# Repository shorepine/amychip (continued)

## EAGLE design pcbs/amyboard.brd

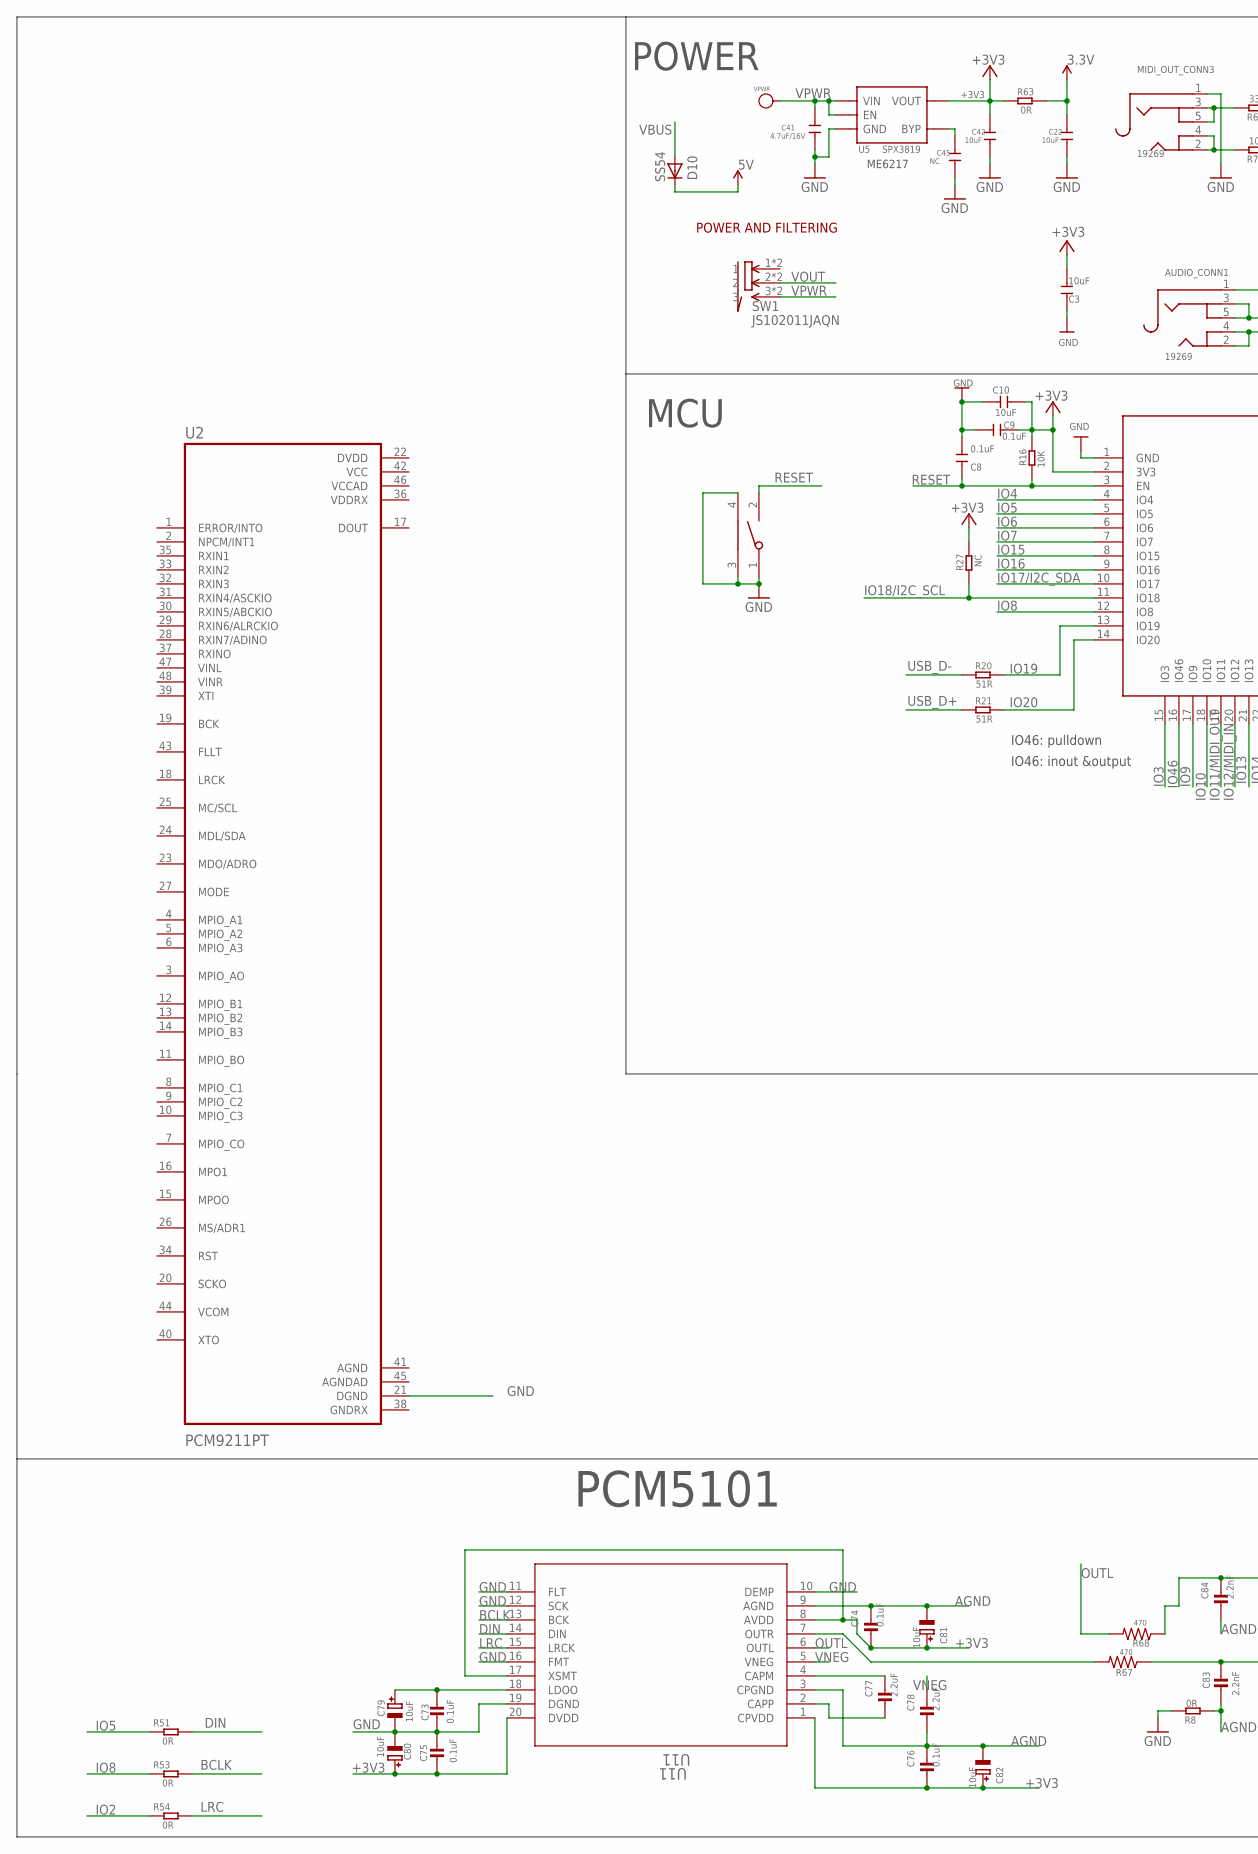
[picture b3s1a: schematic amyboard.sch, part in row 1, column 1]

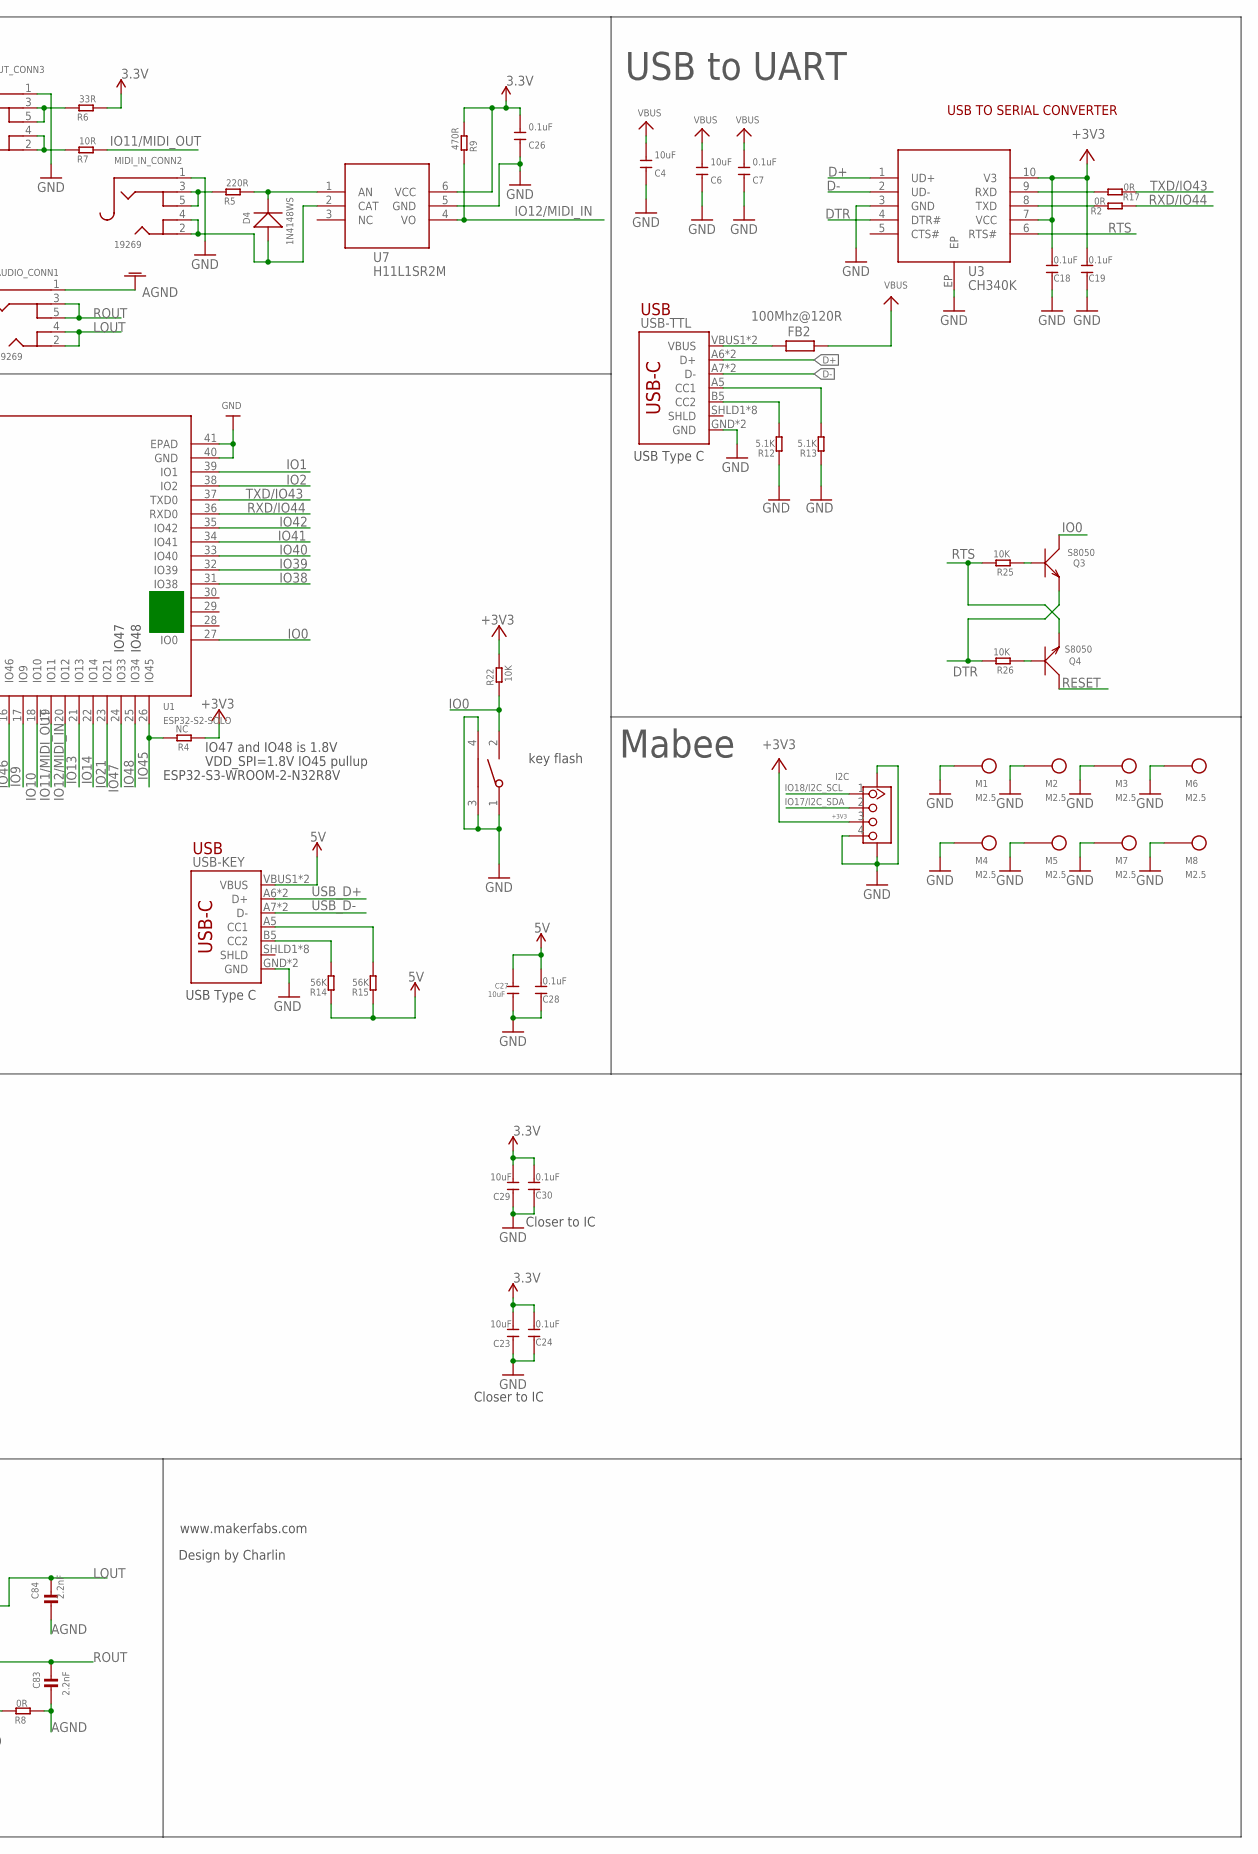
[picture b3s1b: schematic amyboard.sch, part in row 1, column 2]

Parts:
AUDIO_CONN1: 19269; 4UCONN_19269
BOOT: TS24CA; 2*4*3.5MM
C3, C4, C6, C10, C23, C29: 10uF; DISCRETE_C0603
C7, C8, C9, C18, C19, C24, C26, C28, C30: 0.1uF; DISCRETE_C0603
C22, C27, C42: 10uF; 0603
C41: 4.7uF/16V; 0603
C45: NC; 0603
C73, C74, C75, C76: 0.1uF; 0805-NO@1
C77, C78: 2.2uF; 0805-NO@1
C79, C80, C81, C82: 10uF; PANASONIC_C
C83, C84: 2.2nF; 0805-NO@1
D4: 1N4148WS; SOD323
D10: SS54; DO-214AC
FB2: 100Mhz@120R; R0805
I2C: GROVE-CONNECTOR-SMD'90D'; HW4-SMD-2.0-90D
M1, M2, M3, M4, M5, M6, M7, M8: M2.5
MIDI_IN_CONN2: 19269; 4UCONN_19269
MIDI_OUT_CONN3: 19269; 4UCONN_19269
Q3, Q4: S8050; SOT23
R2, R17, R51, R53, R54, R63: 0R; R0603
R4, R27: NC; R0603
R5: 220R; R0603
R6: 33R; R0603
R7: 10R; R0603
R8: 0R; DISCRETE_R0603
R9: 470R; R0603
R12, R13: 5.1K; DISCRETE_R0603
R14, R15: 56K; DISCRETE_R0603
R16, R22, R25, R26: 10K; R0603
R20, R21: 51R; R0603
R67, R68: 470; R0805
RST: TS24CA; 2*4*3.5MM
SW1: JS102011JAQN; SMD-6-2.5MM
U1: ESP32­S2­SOLO; ESP32-­S2-­SOLO
U2: PCM9211PT; QFP50P900X900X160-48N
U3: CH340K; ESOP-10-EP-150MIL
U5: SPX3819; SOT23-5
U7: H11L1SR2M; SOP-6-2.54MM
U11: U11; PW20_TEX
USB-KEY: USB_C5; USB-C-16P-5
USB-TTL: USB_C5; USB-C-16P-5
VPWR: PAD-TEST-POINT-CIRCLE'4545'; TP_4545; PARTNO DNP

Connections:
3.3V: C22.1, C23.2, C24.2, C26.2, C29.2, C30.2, R6.1, R9.1, R63.2, U7.6 (VCC)
5V: C27.1, C28.2, D10.C, R14.1, R15.1, USB-KEY.VBUS1 (VBUS), USB-KEY.VBUS2 (VBUS)
+3V3: C3.2, C9.1, C10.1, C18.2, C19.2, C42.1, C74.2, C75.2, C76.2, C80.+, C81.+, C82.+, I2C.3, R4.1, R16.2, R22.2, R27.2, R63.1, U1.2 (3V3), U3.7 (VCC), U3.10 (V3), U5.5 (VOUT), U11.1 (CPVDD), U11.8 (AVDD), U11.17 (XSMT), U11.20 (DVDD)
AGND: AUDIO_CONN1.1, C74.1, C76.1, C78.2, C81.-, C82.-, C83.2, C84.2, R8.1, U2.41 (AGND), U11.3 (CPGND), U11.9 (AGND)
AGNDAD: U2.45 (AGNDAD)
BCLK: R53.2, U11.13 (BCK)
D+: U3.1 (UD+), USB-TTL.A6 (D+), USB-TTL.B6 (D+)
D-: U3.2 (UD-), USB-TTL.A7 (D-), USB-TTL.B7 (D-)
DIN: R51.2, U11.14 (DIN)
DTR: Q3.2 (E), R26.2, U3.4 (DTR#)
DVDD: U2.22 (DVDD)
GND: BOOT.1, BOOT.3, BOOT.4, C3.1, C4.1, C6.1, C7.1, C8.2, C9.2, C10.2, C18.1, C19.1, C22.2, C23.1, C24.1, C26.1, C27.2, C28.1, C29.1, C30.1, C41.2, C42.2, C45.2, C73.2, C75.1, C79.-, C80.-, I2C.4, I2C.SS1, I2C.SS2, M1.1, M2.1, M3.1, M4.1, M5.1, M6.1, M7.1, M8.1, MIDI_IN_CONN2.1, MIDI_OUT_CONN3.1, R8.2, R12.1, R13.1, RST.1, RST.3, RST.4, U1.1 (GND), U1.40 (GND), U1.41 (EPAD), U2.21 (DGND), U3.3 (GND), U3.EP, U5.2 (GND), U7.5 (GND), U11.10 (DEMP), U11.11 (FLT), U11.12 (SCK), U11.16 (FMT), U11.19 (DGND), USB-KEY.GND, USB-KEY.GND2 (GND), USB-TTL.GND, USB-TTL.GND2 (GND)
GNDRX: U2.38 (GNDRX)
IO0: BOOT.2, Q3.3 (C), R22.1, U1.27 (IO0)
IO1: U1.39 (IO1)
IO2: R54.1, U1.38 (IO2)
IO3: U1.15 (IO3)
IO4: U1.4 (IO4)
IO5: R51.1, U1.5 (IO5)
IO6: U1.6 (IO6)
IO7: U1.7 (IO7)
IO8: R53.1, U1.12 (IO8)
IO9: U1.17 (IO9)
IO10: U1.18 (IO10)
IO11/MIDI_OUT: R7.1, U1.19 (IO11)
IO12/MIDI_IN: R9.2, U1.20 (IO12), U7.4 (VO)
IO13: U1.21 (IO13)
IO14: U1.22 (IO14)
IO15: U1.8 (IO15)
IO16: U1.9 (IO16)
IO17/I2C_SDA: I2C.2, U1.10 (IO17)
IO18/I2C_SCL: I2C.1, R27.1, U1.11 (IO18)
IO19: R20.2, U1.13 (IO19)
IO20: R21.2, U1.14 (IO20)
IO21: U1.23 (IO21)
IO38: U1.31 (IO38)
IO39: U1.32 (IO39)
IO40: U1.33 (IO40)
IO41: U1.34 (IO41)
IO42: U1.35 (IO42)
IO45: R4.2, U1.26 (IO45)
IO46: U1.16 (IO46)
IO47: U1.24 (IO33)
IO48: U1.25 (IO34)
LOUT: AUDIO_CONN1.2, AUDIO_CONN1.4, C84.1, R68.1
LRC: R54.2, U11.15 (LRCK)
unnamed: Q4.1 (B), R26.1
unnamed: Q3.1 (B), R25.1
unnamed: R15.2, USB-KEY.A5 (CC1)
unnamed: R13.2, USB-TTL.A5 (CC1)
unnamed: R12.2, USB-TTL.B5 (CC2)
unnamed: R14.2, USB-KEY.B5 (CC2)
unnamed: FB2.1, USB-TTL.VBUS1 (VBUS), USB-TTL.VBUS2 (VBUS)
unnamed: MIDI_IN_CONN2.3, MIDI_IN_CONN2.5, R5.2
unnamed: D4.-, R5.1, U7.1 (AN)
unnamed: MIDI_OUT_CONN3.3, MIDI_OUT_CONN3.5, R6.2
unnamed: MIDI_OUT_CONN3.2, MIDI_OUT_CONN3.4, R7.2
unnamed: D4.+, MIDI_IN_CONN2.2, MIDI_IN_CONN2.4, U7.2 (CAT)
unnamed: C73.1, C79.+, U11.18 (LDOO)
unnamed: R67.2, U11.7 (OUTR)
unnamed: C77.1, U11.4 (CAPM)
unnamed: R17.2, U3.9 (RXD)
unnamed: C77.2, U11.2 (CAPP)
unnamed: R2.2, U3.8 (TXD)
unnamed: C45.1, U5.4 (BYP)
OUTL: R68.2, U11.6 (OUTL)
RESET: C8.1, Q4.3 (C), R16.1, RST.2, U1.3 (EN)
ROUT: AUDIO_CONN1.3, AUDIO_CONN1.5, C83.1, R67.1
RTS: Q4.2 (E), R25.2, U3.6 (RTS#)
RXD/IO44: R2.1, U1.36 (RXD0)
TXD/IO43: R17.1, U1.37 (TXD0)
USB_D+: R21.1, USB-KEY.A6 (D+), USB-KEY.B6 (D+)
USB_D-: R20.1, USB-KEY.A7 (D-), USB-KEY.B7 (D-)
VBUS: C4.2, C6.2, C7.2, D10.A, FB2.2
VCC: U2.42 (VCC)
VCCAD: U2.46 (VCCAD)
VDDRX: U2.36 (VDDRX)
VNEG: C78.1, U11.5 (VNEG)
VOUT: SW1.2, SW1.2@1 (2)
VPWR: C41.1, SW1.3, SW1.3@1 (3), U5.1 (VIN), U5.3 (EN), VPWR.T

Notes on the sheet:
www.makerfabs.com
Design by Charlin
USB
POWER AND FILTERING
USB TO SERIAL CONVERTER
PCM5101
POWER
USB to UART
USB Type C
Closer to IC
IO46: pulldown
IO46: inout &output
Mabee
MCU
ESP32-S3-WROOM-2-N32R8V
IO47
IO48
ME6217
key flash
IO47 and IO48 is 1.8V
VDD_SPI=1.8V IO45 pullup

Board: 2 copper layers, 86 parts (0 on the bottom side), 54 nets, no tracks yet.

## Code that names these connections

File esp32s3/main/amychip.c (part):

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#define I2S_MCLK  10
#define I2S_BCLK  13 
#define I2S_LRCLK 12
#define AMYOUT 11 // data going to the codec, eg DAC data
#define I2C_SLAVE_SCL 5  
#define I2C_SLAVE_SDA 4 
#define I2C_MASTER_SCL 17
#define I2C_MASTER_SDA 18
#define AMYIN 16 // data coming from the codec, eg ADC  data
#elif defined AMYBOARD_R3
// stuff in the eagle
#define I2S_MCLK  3
#define I2S_BCLK  8
#define I2S_LRCLK 2
#define AMYOUT 6 // data going to the codec, eg DAC data
#define I2C_SLAVE_SCL 5
#define I2C_SLAVE_SDA 4 
#define I2C_MASTER_SCL 18
#define I2C_MASTER_SDA 17
#define AMYIN 9 // data coming from the codec, eg ADC  data
#define MPIO 7 // we don't know what this is, but that's the pin it's connected to 
#endif

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    { 0x6B, 0x00 }, // Main output pins are DIR/ADC AUTO
    { 0x30, 0x04 }, // PLL sends 512fs as SCK
    { 0x31, 0x0A }, // XTI SCK as 512fs too
    { 0x60, 0x44 }, // Initialize PCM9211 DIT to send SPDIF from AUXIN1 through MPO0 (pin15).  MPO1 (pin16) is VOUT (Valid)
    { 0x78, 0x3d }, // MPO0 = 0b1101 = TXOUT, MPO1 = 0b0011 = VOUT
    { 0x6F, 0x40 }  // MPIO_A = CLKST etc / MPIO_B = AUXIN2 / MPIO_C = AUXIN1
};
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    delay_ms(1000);
    

    // make this 1 if you want to actually turn on i2s... it is currently hanging as it can't find MCLK on the pin....
    if(1) {
        check_init(&setup_i2s, "i2s");
        esp_amy_init();
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
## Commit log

2024-10-01 adding wm8960 setup code
2024-10-01 works with AMY audio in on tulip
2024-10-03 cleaning this up for multi chip
2024-10-03 up to date with latest AMY branch
2024-10-05 Draw attention to audio out GND is *not* GND
2024-10-05 Explicitly note that esp-idf 5.2 won't work.
2024-10-05 Seems you need to cd into esp32s3 before idf.py flash.
2024-11-06 adding pcbs
2024-11-19 Added pcm9211.txt with hookup information for dpwe PCM9211 ADC/SPDIF_IO devboard.
2024-11-19 pcm9211: Added description of dpwe devboard wiring. Added PCM9211 Arduino test sketch.
2024-11-19 pcm9211 hookup image
2024-11-23 amy as submodule
2024-11-23 use AMY module instead
2024-11-23 esp-idf i2c pcm9211 setup
2024-11-24 Add PCM9211 setup & format conversion; updated pcm9211.txt for I2S->SPDIF out.
2024-11-24 Fix buffer sizes for i2s system calls.
2024-11-25 i2s not working, but reads registers and sets up i2s follower like the espressif test case does..
2024-11-25 0x62
2024-11-26 adding start of amyboard schematic
2024-11-26 deleting old amyboard rev
2024-11-26 Working for copying I2S in to I2S out, PCM9211 + PCM5102A.
2024-11-26 Fixed i2s_config bit_shift so AMY output works with right bit interpretation.
2024-11-27 @dpwe's very important comments
2024-11-27 Added caps and PLL filter to schematic.
2024-11-27 remving eagle cruft
2024-11-27 caps
2024-11-27 moving to 3.5mm jacks for everything
2024-11-28 stacked audio jacks
2024-11-28 dac/adcs
2024-11-28 header, fixed adcs
2024-11-30 adding r4 board with no UART chip and sd card
2024-11-30 moving around
2024-12-02 r4 with top jacks
2024-12-07 moving jacks together on bottom
2024-12-09 adding parts for amyboard
2024-12-10 Added 8413, TL074, DIP switch, +/-12V rails to schematic.
2024-12-11 removing other boost
2024-12-11 4 way DIN, VPWR
2024-12-11 copying to r5
2024-12-11 adding back in dan's r4
2024-12-11 CVOUT fixes
2024-12-11 dans fixes
2024-12-11 gitignore
2024-12-11 ADC cap in parallel
2024-12-11 right side up
2024-12-11 moving parts
2024-12-27 Added ferrite beads in Pi circuits to + and -12v lines.
2024-12-28 Moved GP8413 and 5V LDO to +12V_UNFILTERED.
2024-12-28 copying usb fb
2025-03-04 fixes so it builds/runs on AMYboard v0
2025-03-04 nicer way of setting regs and testing them
2025-03-04 mpio0?
